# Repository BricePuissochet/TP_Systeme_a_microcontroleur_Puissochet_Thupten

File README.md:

# TP_Systeme_a_microcontroleur_Puissochet_Thupten

1.2 Le microcontrôleur sous KiCAD

Q13)  Pourquoi PB9 est relié à la masse ? (Répondez à cette question, et aux sui-
vantes, dans le README du repo git.)
Le PB9 est le boot, nous le relions à la masse car comme ca on boot dans le usermemory.

Q14) Quel est le rôle de L1, C5 et C7 ?
L1, C5 et C7 sont des composants qui filtre notre alimentation.

1.3 Le reste du schéma

Q3). Quelle page de la datasheet indique les valeurs des condensateurs ?
La page de la datasheet ou ce trouve les valeurs est la pages 3.

Q5) Quelle page de la datasheet nous indique les valeurs de condensateurs ?
La page de la datasheet ou ce trouve les valeurs est la pages 6.

Q6) Quel est le rôle de la broche CS ?
Cette broche nous sert d'Enable pour la communication SPI.

Q7) Quel est le rôle de la broche LDAC ?
Cette broche nous sert de synchronisation pour le DAC.

Q8) Pourquoi le signal MISO n’est pas utilisé ?
Il n'y a pas de communication entre le DAC est le master, donc nous avons pas besoin de MISO

Q10) Où trouve-t-on les indications du pinout du connecteur SWD ?
On trouve les indications dans la datasheet page 19 dans Virtual COM port.

1.4 Affectation des empreintes

Q3) Que signifie 0805 ? 0603 ? 1206 ?
Ceci indique la tailles des empreintes, le condencateur est de taille 0.8mm sur 0.5mm

Q4) Que signifie LQFP ? SOT-223 ? SOIC ? Ne vous contentez pas de donner le sigle,
j’attends une petite description (vous pouvez copier-coller depuis wikipedia,
mais lisez avant quand même))
Ceci correspond à la l'empreinte du boitier en fonction du type de boitier.

3.1 Activation des LL drivers

Q4) Que signifie __STATIC_INLINE ?
STATIC_INLINE signifie que la fonction est visible ou elle est declaré et qui indique au compilateur d'implementer le corps de la focntion.

Q5)Et pourquoi y a-t-il du code dans un .h alors que Môssieur Fiack vous a expres-
sément demandé de pas le faire ? (Les deux questions sont peut-être liés, va
savoir)

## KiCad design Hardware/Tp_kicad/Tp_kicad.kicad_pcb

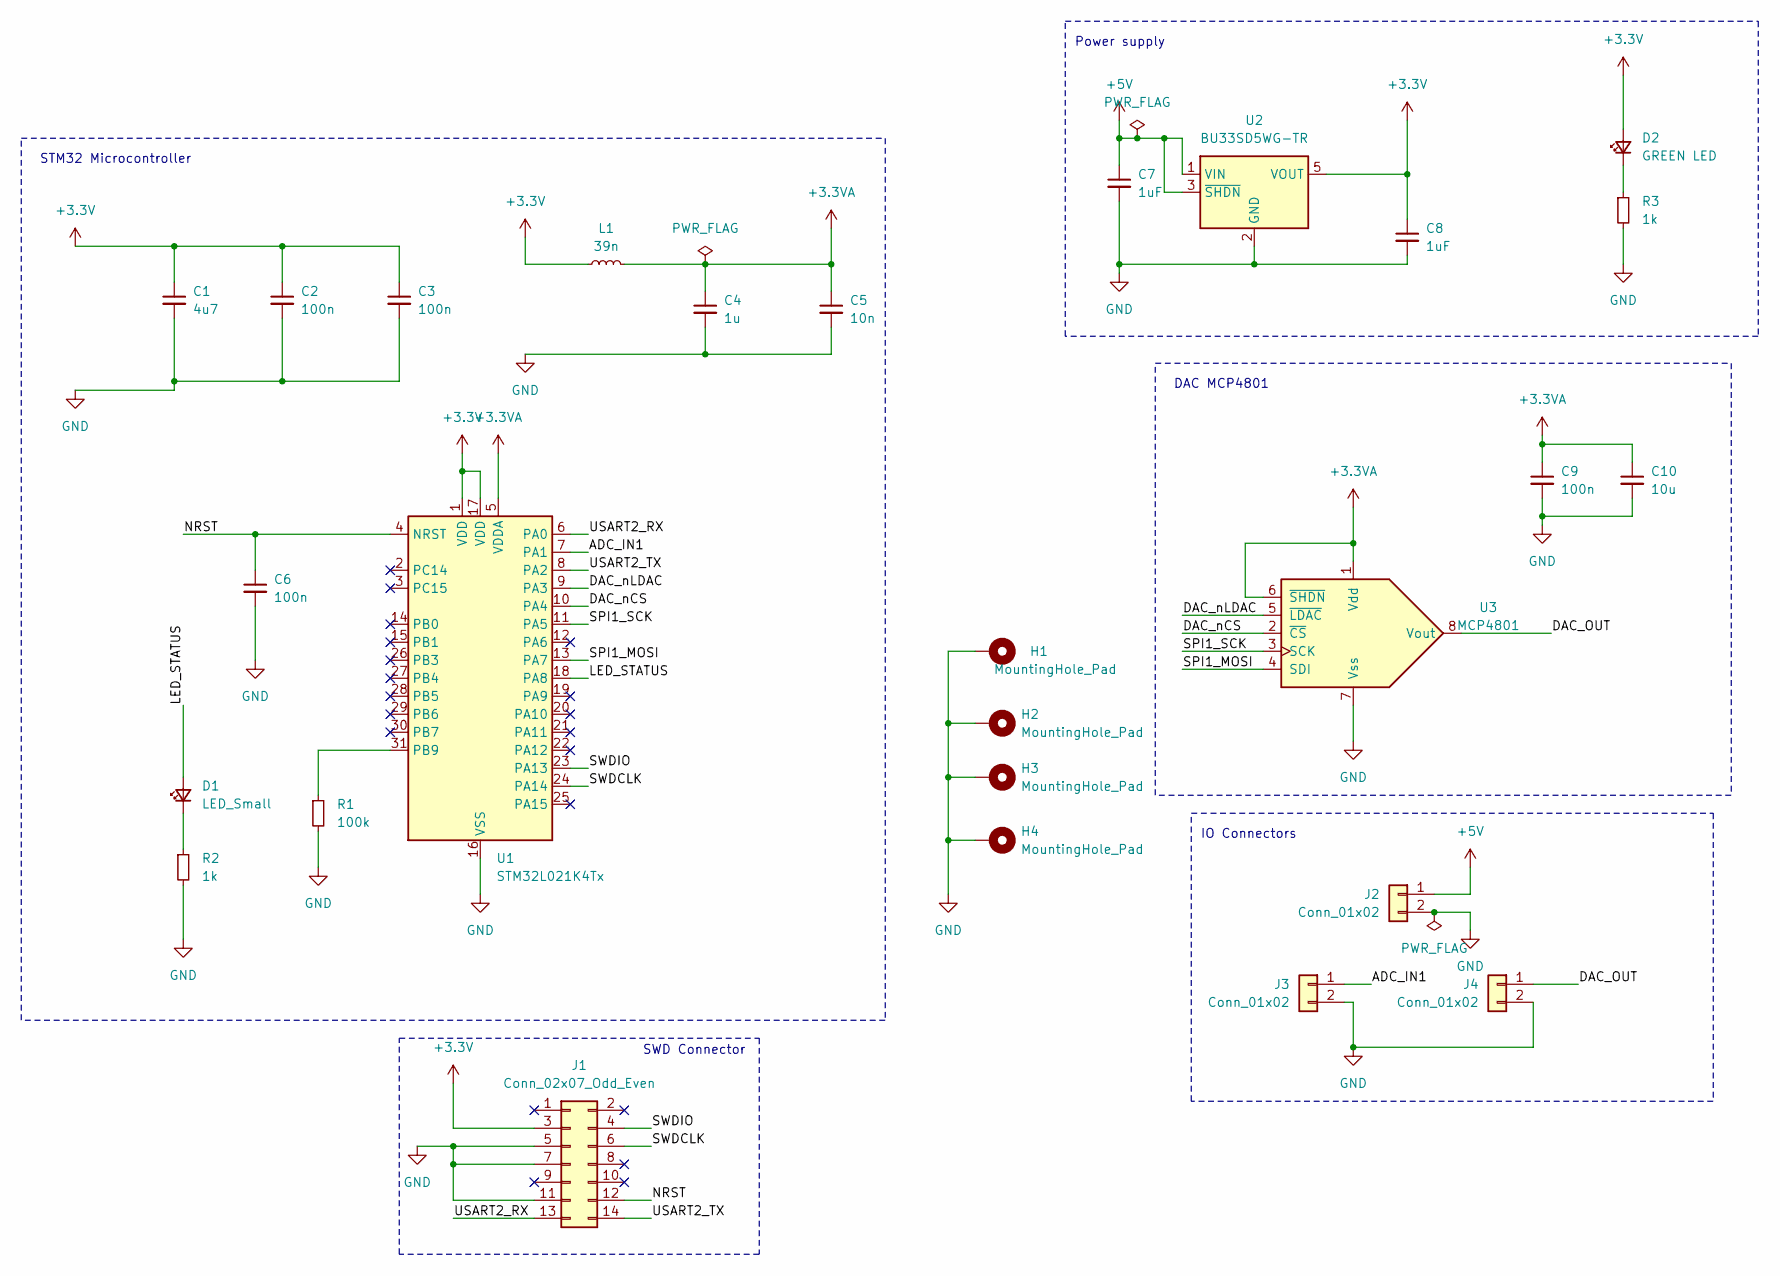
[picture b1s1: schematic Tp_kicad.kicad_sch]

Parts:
C1: 4u7; C_0805_2012Metric_Pad1.18x1.45mm_HandSolder
C2, C3, C6, C9: 100n; C_0805_2012Metric_Pad1.18x1.45mm_HandSolder
C4: 1u; C_0805_2012Metric_Pad1.18x1.45mm_HandSolder
C5: 10n; C_0805_2012Metric_Pad1.18x1.45mm_HandSolder
C7, C8: 1uF; C_0805_2012Metric
C10: 10u; C_0805_2012Metric
D1: LED_Small; LED_0603_1608Metric_Pad1.05x0.95mm_HandSolder
D2: GREEN LED; LED_0603_1608Metric_Pad1.05x0.95mm_HandSolder
H1, H2, H3, H4: MountingHole_Pad; MountingHole_3.2mm_M3_Pad
J1: Conn_02x07_Odd_Even; PinHeader_2x07_P1.27mm_Vertical_SMD
J2, J3, J4: Conn_01x02; JST_XH_B2B-XH-A_1x02_P2.50mm_Vertical
L1: 39n; L_0805_2012Metric_Pad1.05x1.20mm_HandSolder
R1: 100k; R_0805_2012Metric_Pad1.20x1.40mm_HandSolder
R2, R3: 1k; R_0805_2012Metric_Pad1.20x1.40mm_HandSolder
U1: STM32L021K4Tx; LQFP-32_7x7mm_P0.8mm
U2: BU33SD5WG-TR; SOT-23-5
U3: MCP4801; SOIC-8_3.9x4.9mm_P1.27mm

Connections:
+3.3V: C1.1, C2.1, C3.1, C8.1, D2.2 (A), J1.3, L1.1, U1.1 (VDD), U1.17 (VDD), U2.5 (VOUT)
+3.3VA: C4.1, C5.1, C9.1, C10.1, L1.2, U1.5 (VDDA), U3.1 (Vdd), U3.6 (~SHDN)
+5V: C7.1, J2.1, U2.1 (VIN), U2.3 (~SHDN)
/ADC_IN1: J3.1, U1.7 (PA1)
/DAC_OUT: J4.1, U3.8 (Vout)
/DAC_nCS: U1.10 (PA4), U3.2 (~CS)
/DAC_nLDAC: U1.9 (PA3), U3.5 (~LDAC)
/LED_STATUS: D1.2 (A), U1.18 (PA8)
/NRST: C6.1, J1.12, U1.4 (NRST)
/SPI1_MOSI: U1.13 (PA7), U3.4 (SDI)
/SPI1_SCK: U1.11 (PA5), U3.3 (SCK)
/SWDCLK: J1.6, U1.24 (PA14)
/SWDIO: J1.4, U1.23 (PA13)
/USART2_RX: J1.13, U1.6 (PA0)
/USART2_TX: J1.14, U1.8 (PA2)
GND: C1.2, C2.2, C3.2, C4.2, C5.2, C6.2, C7.2, C8.2, C9.2, C10.2, H1.1, H2.1, H3.1, H4.1, J1.5, J1.7, J1.11, J2.2, J3.2, J4.2, R1.2, R2.2, R3.2, U1.16 (VSS), U1.32 (VSS), U2.2 (GND), U3.7 (Vss)
unnamed: D1.1 (K), R2.1
unnamed: D2.1 (K), R3.1
unnamed: R1.1, U1.31 (PB9)

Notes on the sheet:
DAC MCP4801
STM32 Microcontroller
SWD Connector
IO Connectors
Power supply

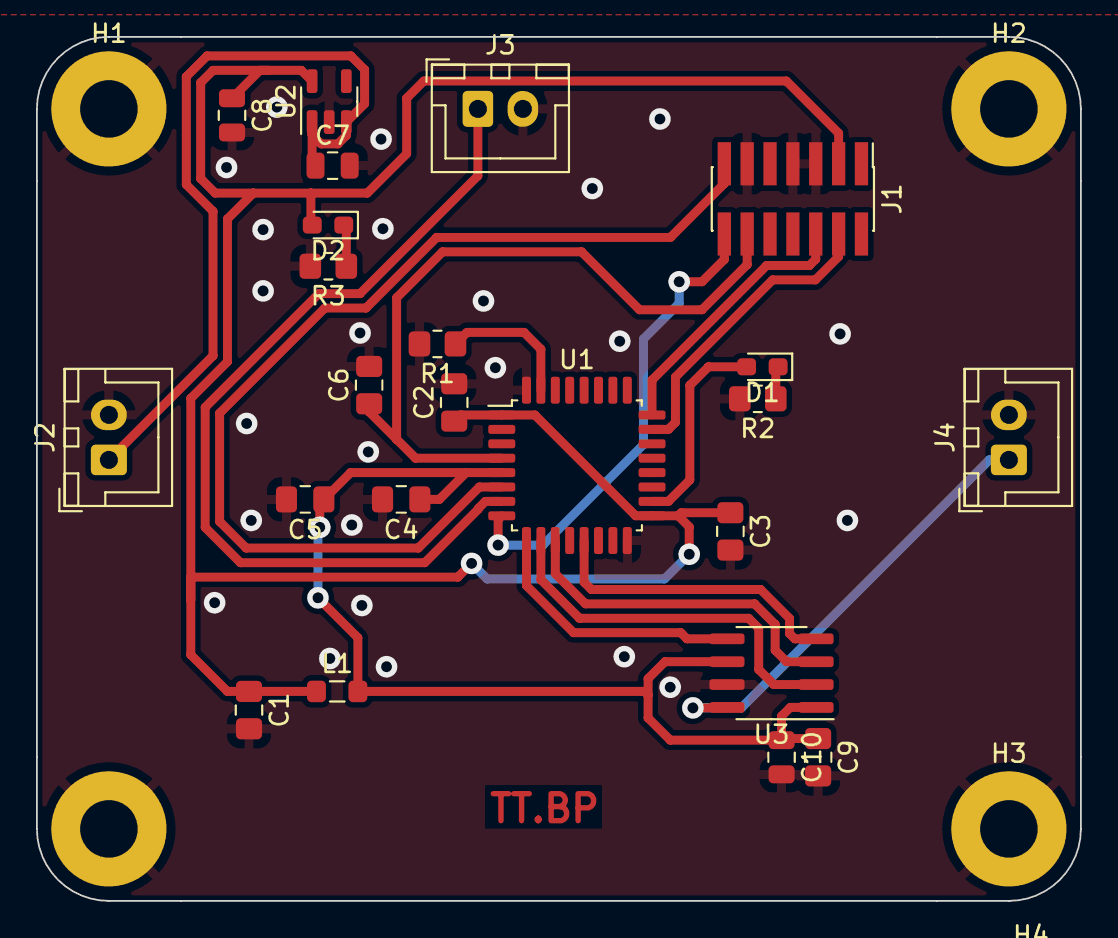
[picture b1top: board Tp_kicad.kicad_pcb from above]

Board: 2 copper layers, 58.0 x 48.0 mm, 27 parts (0 on the bottom side), 19 nets.

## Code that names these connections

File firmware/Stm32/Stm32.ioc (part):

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Mcu.Name=STM32L021K4Tx
Mcu.Package=LQFP32
Mcu.UserName=STM32L021K4Tx
PA0-CK_IN.Mode=Asynchronous
PA0-CK_IN.Signal=USART2_RX
PA13.Mode=Serial_Wire
PA13.Signal=SYS_SWDIO
PA14.Mode=Serial_Wire
PA14.Signal=SYS_SWCLK
PA2.Mode=Asynchronous
PA2.Signal=USART2_TX
PA3.GPIOParameters=GPIO_Label
PA3.GPIO_Label=DAC_nLDAC
PA3.Signal=GPIO_Input
PA4.GPIOParameters=GPIO_Label
PA4.GPIO_Label=DAC_nCS
PA4.Signal=GPIO_Output
PA5.Mode=Simplex_Bidirectional_Master
PA5.Signal=SPI1_SCK
PA7.Mode=Simplex_Bidirectional_Master
PA7.Signal=SPI1_MOSI
PA8.Signal=S_TIM2_CH1
RCC.HSE_VALUE=8000000
RCC.SYSCLKFreq_VALUE=16000000
RCC.SYSCLKSource=RCC_SYSCLKSOURCE_HSI
board=custom

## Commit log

2024-02-27 stm32l021k4.pdf
2024-02-27 stlinker.pdf
2024-02-27 firmware
2024-02-27 RoutagePCB
2024-02-29 commmit
